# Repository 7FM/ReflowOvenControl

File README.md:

# ReflowOvenControl
This repo is a combination of the following great projects:
- https://github.com/dasaki/nanoReflowController
- https://github.com/0xPIT/reflowOvenController
- https://github.com/engineertype/Controleo3.git

with the focus of using the UI schemes of the first two projects and using the profile management & control algorithms from [Controleo3](https://www.whizoo.com/).

The whole project targets an Arduino Nano and therefore almost all used Libraries where optimized for space and sometimes for performance too.

## Profiles
As mentiened before this projects uses the Controleo Profile Management but with a reduced Token set (see: src/read_profiles.cpp or include/read_profiles.hpp).
A good overview for all tokens(also non supported ones) with explanation can be found [here](https://www.whizoo.com/profiles).

## Hardware
- Arduino Nano
- 1.8'' Color TFT display (ST7735R) as from Adafruit: https://www.adafruit.com/product/358 (can be replaced with serial UI only)
- Rotary Encoder (can be replaced with serial UI only)
- SD Card reader
- Thermocouple reader (MAX6675)
- Buzzer (optional)
- Servo (optional)
- SSR or something to control the oven
- oven to be controlled
- cooling fan (optional)
- convection fan (optional)

For convenience a custom PCB was created using [KiCad](https://www.kicad.org/) but is not mandatory.
Please note that I am no professional (resistors & transistor were arbitrarily chosen by own availability) so any use of the PCB at your own risk!
I also designed some 3D Models using [FreeCAD](https://www.freecadweb.org/) for mounting the hardware.

## Building
Clone the repository with `git clone --recursive` as submodules are used.
If already cloned, the submodules can also be downloaded afterwards using: `git submodule update --init --recursive`.
For compiling simply use [PlatformIO](https://platformio.org/).

## Configuration
Features, Pins & more can be configured in `src/config.h`. Feel free to ask if the impact of certain options is unclear.

## Useful ressources
- https://ww1.microchip.com/downloads/en/DeviceDoc/Atmel-7810-Automotive-Microcontrollers-ATmega328P_Datasheet.pdf
- https://academy.cba.mit.edu/classes/embedded_programming/doc1022.pdf
- http://ww1.microchip.com/downloads/en/DeviceDoc/Atmel-0856-AVR-Instruction-Set-Manual.pdf

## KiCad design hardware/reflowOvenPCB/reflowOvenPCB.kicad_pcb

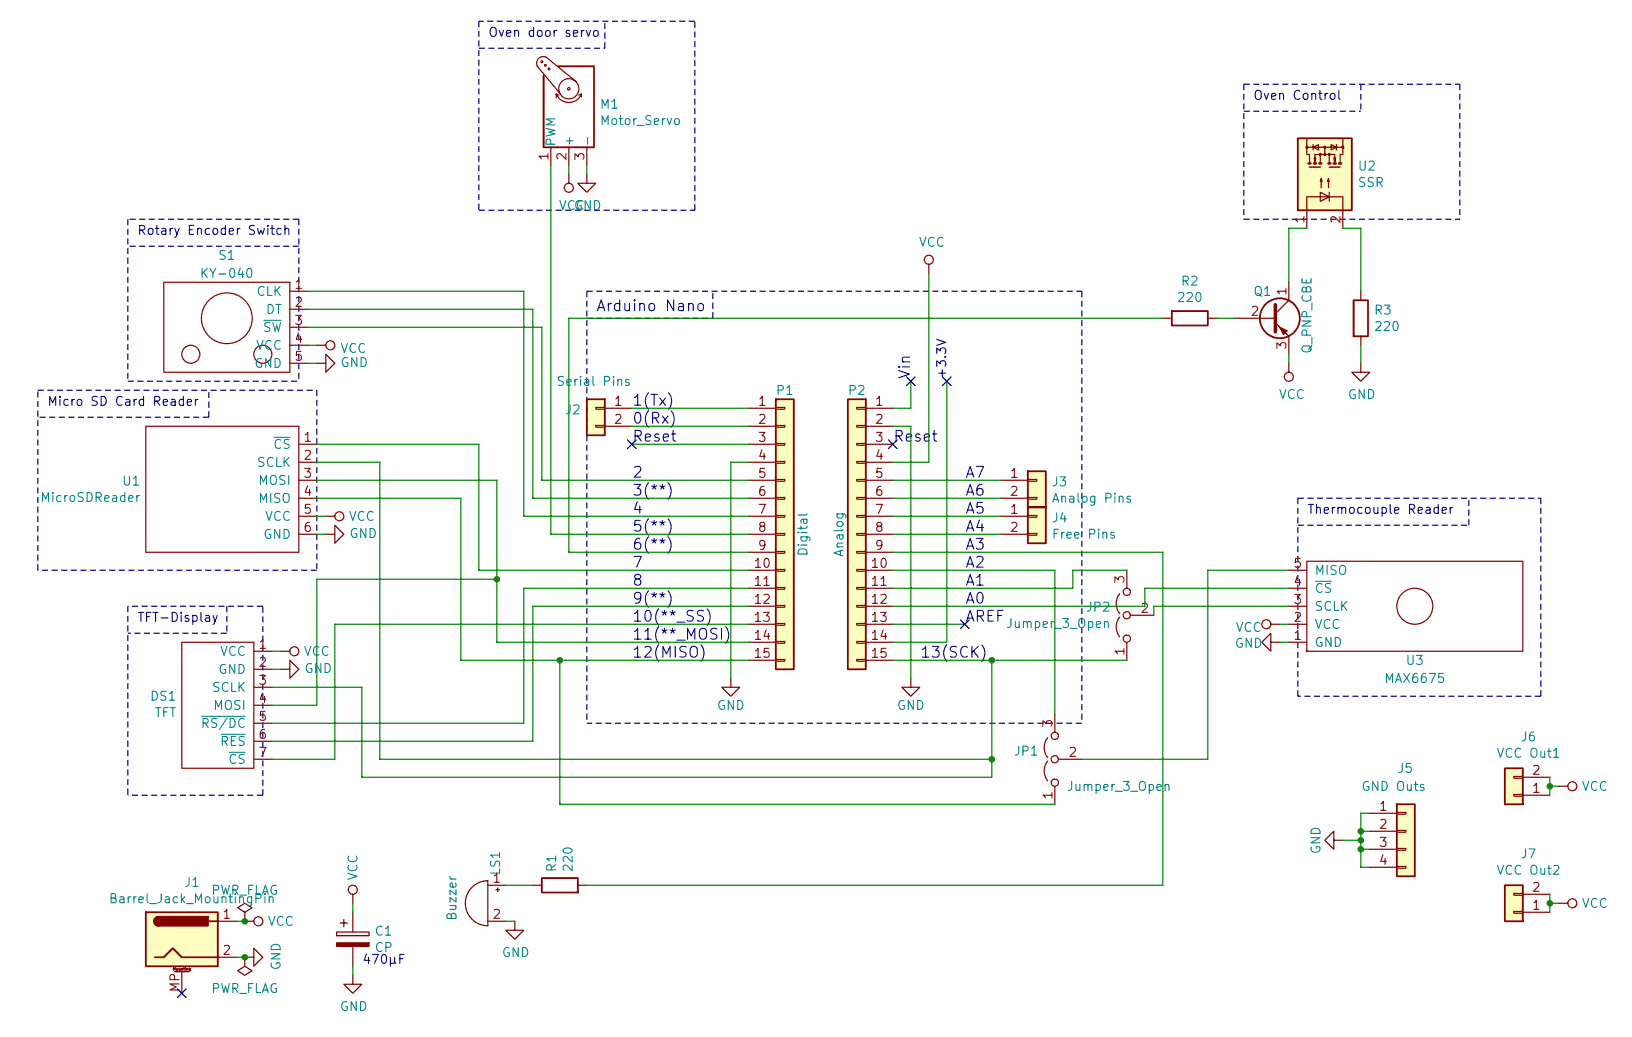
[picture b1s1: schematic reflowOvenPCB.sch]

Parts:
C1: CP; CP_Radial_D8.0mm_P3.50mm
DS1: TFT; PinHeader_1x07_P2.54mm_Vertical
J1: Barrel_Jack_MountingPin; BarrelJack_Horizontal
J2: Serial Pins; PinHeader_1x02_P2.54mm_Vertical
J3: Analog Pins; PinHeader_1x02_P2.54mm_Vertical
J4: Free Pins; PinHeader_1x02_P2.54mm_Vertical
J5: GND Outs; PinSocket_1x04_P2.54mm_Vertical
J6: VCC Out1; PinSocket_1x02_P2.54mm_Vertical
J7: VCC Out2; PinSocket_1x02_P2.54mm_Vertical
JP1, JP2: Jumper_3_Open; PinHeader_1x03_P2.54mm_Vertical
LS1: Buzzer; Buzzer_12x9.5RM7.6
M1: Motor_Servo; PinHeader_1x03_P2.54mm_Vertical
P1: Digital; Socket_Strip_Arduino_1x15
P2: Analog; Socket_Strip_Arduino_1x15
Q1: Q_PNP_CBE; TO-92_Inline_Wide
R1, R2, R3: 220; R_Axial_DIN0207_L6.3mm_D2.5mm_P7.62mm_Horizontal
S1: KY-040; PinHeader_1x05_P2.54mm_Vertical
U1: MicroSDReader; PinHeader_1x06_P2.54mm_Vertical
U2: SSR; PinHeader_1x02_P2.54mm_Vertical
U3: MAX6675; PinHeader_1x05_P2.54mm_Vertical

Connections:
GND: C1.2, DS1.2 (GND), J1.2, J5.1, J5.2, J5.3, J5.4, LS1.2 (+), M1.3 (-), P1.4, P2.2, R3.2, S1.5 (GND), U1.6 (GND), U3.1 (GND)
unnamed: DS1.3 (SCLK), JP2.1 (A), P2.15, U1.2 (SCLK)
unnamed: DS1.4 (MOSI), P1.14, U1.3 (MOSI)
unnamed: DS1.5 (~RS/DC), P1.11
unnamed: DS1.6 (~RES), P1.12
unnamed: DS1.7 (~CS), P1.13
unnamed: J2.1, P1.1
unnamed: J2.2, P1.2
unnamed: J3.1, P2.5
unnamed: J3.2, P2.6
unnamed: J4.1, P2.7
unnamed: J4.2, P2.8
unnamed: JP1.1 (A), P1.15, U1.4 (MISO)
unnamed: JP1.2 (C), U3.5 (MISO)
unnamed: JP1.3 (B), P2.10
unnamed: JP2.2 (C), U3.3 (SCLK)
unnamed: JP2.3 (B), P2.11
unnamed: LS1.1 (-), R1.1
unnamed: M1.1 (PWM), P1.8
unnamed: P1.5, S1.3 (~SW)
unnamed: P1.6, S1.2 (DT)
unnamed: P1.7, S1.1 (CLK)
unnamed: P1.9, R2.2
unnamed: P1.10, U1.1 (~CS)
unnamed: P2.9, R1.2
unnamed: P2.12, U3.4 (~CS)
unnamed: Q1.1 (C), U2.1
unnamed: Q1.2 (B), R2.1
unnamed: R3.1, U2.2
VCC: C1.1, DS1.1 (VCC), J1.1, J6.1, J6.2, J7.1, J7.2, M1.2 (+), P2.4, Q1.3 (E), S1.4 (VCC), U1.5 (VCC), U3.2 (VCC)

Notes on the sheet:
Arduino Nano
Rotary Encoder Switch
TFT-Display
Oven Control
Oven door servo
Micro SD Card Reader
Thermocouple Reader
Reset
0(Rx)
1(Tx)
AREF
11(**_MOSI)
12(MISO)
10(**_SS)
9(**)
6(**)
5(**)
3(**)
13(SCK)
Vin
+3.3V
470µF

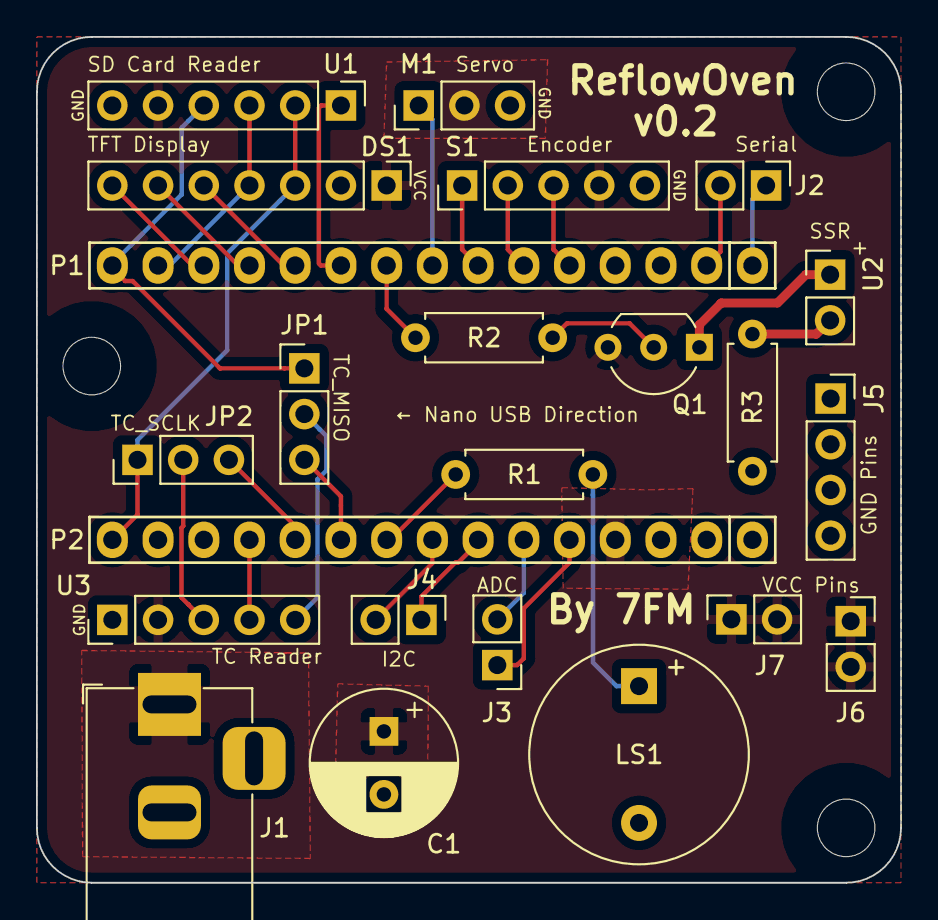
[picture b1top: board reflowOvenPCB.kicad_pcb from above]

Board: 2 copper layers, 48.0 x 47.0 mm, 23 parts (0 on the bottom side), 30 nets.

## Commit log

2020-11-07 inital commit
2020-11-07 first readme draft
2020-11-07 improve README
2020-11-07 add kicad project & freecad designes
2020-11-09 fix adafruit lib_deps (with default config not used but causes compile errors)
2020-12-07 Remove unsave optimization flag
    See: https://github.com/MarlinFirmware/Marlin/pull/20389
2022-07-08 fix typo
2022-07-09 Add LICENSE
2024-03-19 nix setup, make compile with newer platformio versions
2024-03-19 fix FastPin library header not found
